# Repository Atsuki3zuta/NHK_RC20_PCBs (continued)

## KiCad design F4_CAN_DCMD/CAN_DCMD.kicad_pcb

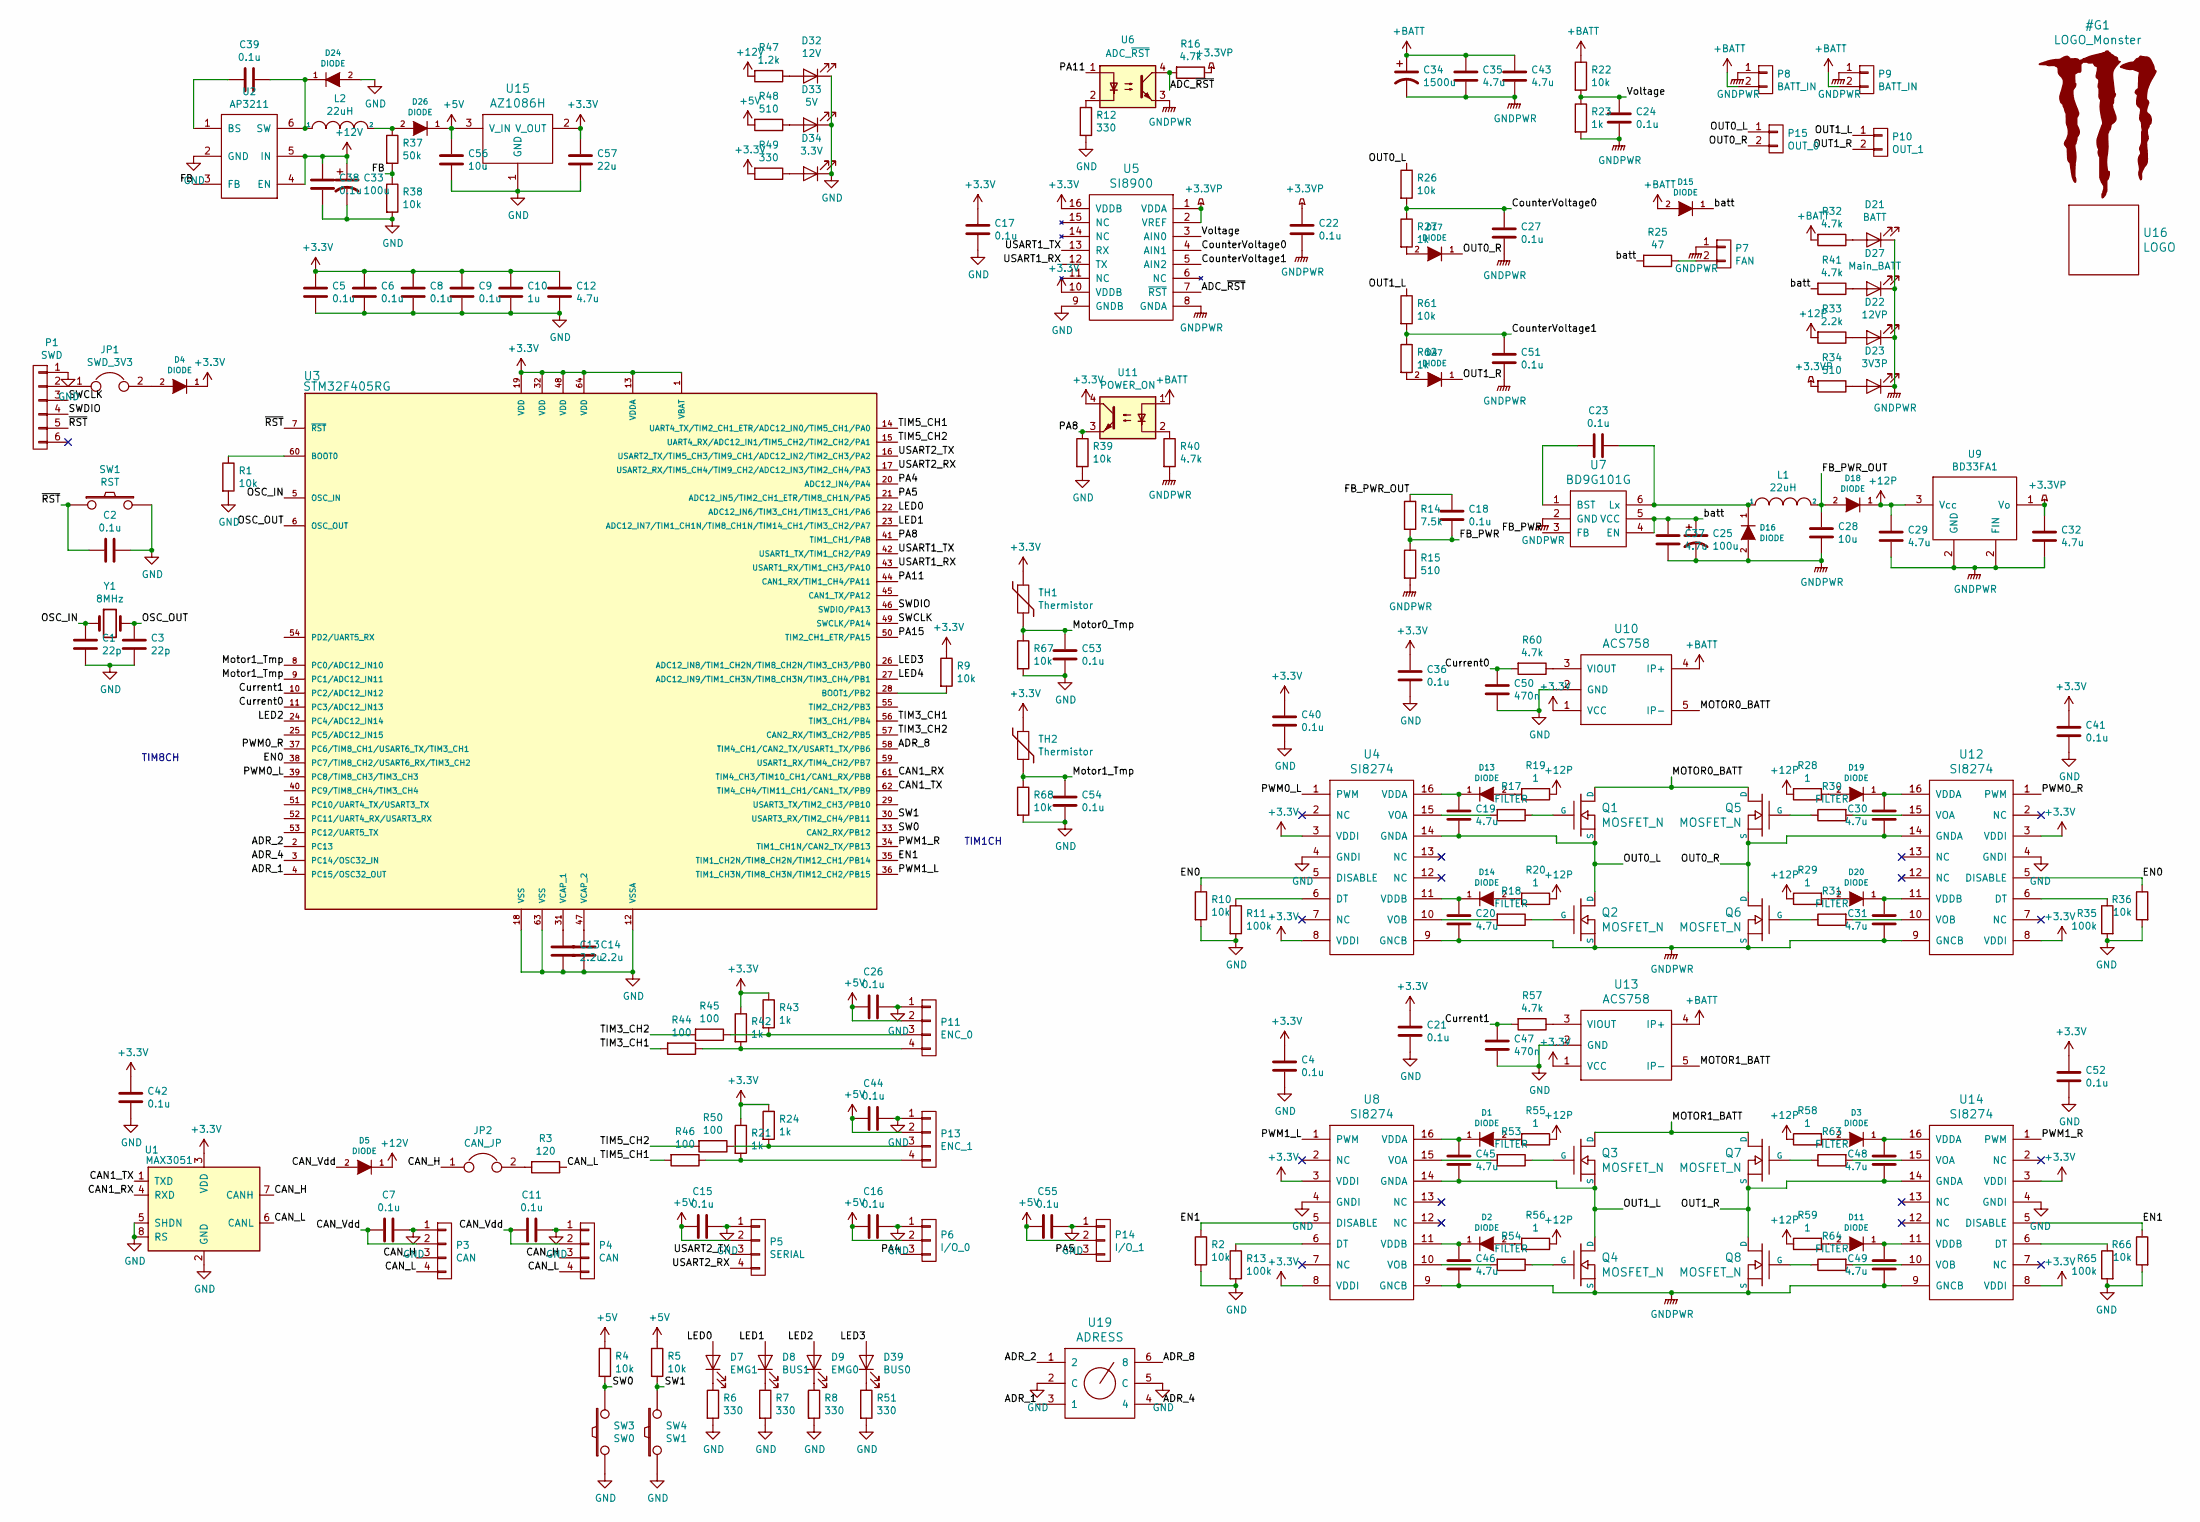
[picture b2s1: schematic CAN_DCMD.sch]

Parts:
C1, C3: 22p; C_0603_1608Metric
C2, C4, C5, C6, C7, C8, C9, C11, C15, C16, C17, C18, C21, C22, C23, C24, C26, C27, C36, C38, C39, C40, C41, C42, C44, C51, C52, C53, C54, C55: 0.1u; C_0603_1608Metric
C10: 1u; C_0603_1608Metric
C12: 4.7u; C_0603_1608Metric
C13, C14: 2.2u; C_0603_1608Metric
C19, C20, C30, C31, C45, C46, C48, C49: 4.7u; C_1210_3225Metric
C25, C33: 100u; CP_Radial_D5.0mm_P2.50mm
C28: 10u; C_0805_2012Metric
C29, C32, C35, C37, C43: 4.7u; C_0805_2012Metric
C34: 1500u; CP_Radial_D10.0mm_P5.00mm
C47, C50: 470n; C_0603_1608Metric
C56: 10u; C_0603_1608Metric
C57: 22u; C_0603_1608Metric
D1, D2, D3, D11, D13, D14, D19, D20: DIODE; D_0603_1608Metric
D4, D5, D16, D17, D18, D24, D26, D47: DIODE; D_SOD-123
D7: EMG1; LED_0603_1608Metric
D8: BUS1; LED_0603_1608Metric
D9: EMG0; LED_0603_1608Metric
D15: DIODE; D_SMA
D21: BATT; LED_0603_1608Metric
D22: 12VP; LED_0603_1608Metric
D23: 3V3P; LED_0603_1608Metric
D27: Main_BATT; LED_0603_1608Metric
D32: 12V; LED_0603_1608Metric
D33: 5V; LED_0603_1608Metric
D34: 3.3V; LED_0603_1608Metric
D39: BUS0; LED_0603_1608Metric
JP1: SWD_3V3; SolderJumper-2_P1.3mm_Open_TrianglePad1.0x1.5mm
JP2: CAN_JP; PinHeader_1x02_P2.54mm_Vertical
L1, L2: 22uH; Inductor_Taiyo-Yuden_NR-60xx_HandSoldering
P1: SWD; ZH_6P
P3, P4: CAN; XA_4LC
P5: SERIAL; XA_4LC
P6: I/O_0; XA_3LC
P7: FAN; XA_2P
P8: BATT_IN; XT60_M
P9: BATT_IN; XT60_F
P10: OUT_1; XT60_F
P11: ENC_0; XA_4LC
P13: ENC_1; XA_4LC
P14: I/O_1; XA_3LC
P15: OUT_0; XT60_F
Q1, Q2, Q3, Q4, Q5, Q6, Q7, Q8: MOSFET_N; D2-PAK_compact
R1, R2, R4, R5, R9, R10, R22, R26, R36, R38, R39, R61, R66, R67, R68: 10k; R_0603_1608Metric
R3: 120; R_0603_1608Metric
R6, R7, R8, R12, R49, R51: 330; R_0603_1608Metric
R11, R13, R35, R65: 100k; R_0603_1608Metric
R14: 7.5k; R_0603_1608Metric
R15, R34, R48: 510; R_0603_1608Metric
R16, R32, R40, R41, R57, R60: 4.7k; R_0603_1608Metric
R17, R18, R30, R31, R53, R54, R63, R64: FILTER; R_0603_1608Metric
R19, R20, R28, R29, R55, R56, R58, R59: 1; R_0603_1608Metric
R21, R23, R24, R27, R42, R43, R62: 1k; R_0603_1608Metric
R25: 47; R_2812
R33: 2.2k; R_0603_1608Metric
R37: 50k; R_0603_1608Metric
R44, R45, R46, R50: 100; R_0603_1608Metric
R47: 1.2k; R_0603_1608Metric
SW1: RST; SW_SPST_CK_RS282G05A3
SW3: SW0; SW_SPST_CK_RS282G05A3
SW4: SW1; SW_SPST_CK_RS282G05A3
TH1, TH2: Thermistor; C_0603_1608Metric
U1: MAX3051; SOIC-8_3.9x4.9mm_P1.27mm
U2: AP3211; TSOP-6_1.65x3.05mm_P0.95mm
U3: STM32F405RG; LQFP-64_10x10mm_P0.5mm
U4, U8, U12, U14: SI8274; SOIC-16W_5.3x10.2mm_P1.27mm
U5: SI8900; SOIC-16W_7.5x10.3mm_P1.27mm
U6: ADC_~RST; SO-4_4.4x2.3mm_P1.27mm
U7: BD9G101G; TSOP-6_1.65x3.05mm_P0.95mm
U9: BD33FA1; SOT-89-3
U10, U13: ACS758; ACS785xCB
U11: POWER_ON; SO-4_4.4x2.3mm_P1.27mm
U15: AZ1086H; SOT-223-3_TabPin2
U16: LOGO; Mini_Monster
U19: ADRESS; rotary_0F
Y1: 8MHz; Crystal_SMD_5032_2Pads

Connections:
+3.3VP: C22.1, C32.1, R16.1, R34.2, U5.1 (VDDA), U5.2 (VREF), U9.1 (Vo)
+3V3: C4.1, C5.1, C6.1, C8.1, C9.1, C10.1, C12.1, C17.1, C21.1, C36.1, C40.1, C41.1, C42.1, C52.1, C57.1, D4.1 (K), R9.1, R21.1, R24.1, R42.1, R43.1, R49.2, TH1.1, TH2.1, U1.3 (VDD), U3.1 (VBAT), U3.13 (VDDA), U3.19 (VDD), U3.32 (VDD), U3.48 (VDD), U3.64 (VDD), U4.3 (VDDI), U4.8 (VDDI), U5.10 (VDDB), U5.16 (VDDB), U8.3 (VDDI), U8.8 (VDDI), U10.1 (VCC), U11.4, U12.3 (VDDI), U12.8 (VDDI), U13.1 (VCC), U14.3 (VDDI), U14.8 (VDDI), U15.2 (V_OUT)
+5V: C15.2, C16.2, C26.2, C44.2, C55.2, C56.1, D26.1 (K), P5.2, P6.2, P11.2, P13.2, P14.2, R4.1, R5.1, R48.2, U15.3 (V_IN)
+12P: C29.1, D18.1 (K), R19.1, R20.1, R28.1, R29.1, R33.2, R55.1, R56.1, R58.1, R59.1, U9.3 (Vcc)
+12V: C33.1, C38.1, D5.1 (K), R47.2, U2.4 (EN), U2.5 (IN)
+BATT: C34.1, C35.1, C43.1, D15.2 (A), P8.2, P9.2, R22.1, R32.2, U10.4 (IP+), U11.1, U13.4 (IP+)
/ADC_~RST: R16.2, U5.7 (~RST~), U6.4
/ADR_1: U3.4 (PC15/OSC32_OUT), U19.3 (1)
/ADR_2: U3.2 (PC13), U19.1 (2)
/ADR_4: U3.3 (PC14/OSC32_IN), U19.4
/ADR_8: U3.58 (TIM4_CH1/CAN2_TX/USART1_TX/PB6), U19.6 (8)
/CAN1_RX: U1.4 (RXD), U3.61 (TIM4_CH3/TIM10_CH1/CAN1_RX/PB8)
/CAN1_TX: U1.1 (TXD), U3.62 (TIM4_CH4/TIM11_CH1/CAN1_TX/PB9)
/CAN_H: JP2.1, P3.3, P4.3, U1.7 (CANH)
/CAN_L: P3.4, P4.4, R3.1, U1.6 (CANL)
/CAN_Vdd: C7.2, C11.2, D5.2 (A), P3.2, P4.2
/CounterVoltage0: C27.1, R26.2, R27.1, U5.4 (AIN1)
/CounterVoltage1: C51.1, R61.2, R62.1, U5.5 (AIN2)
/Current0: C50.1, R60.2, U3.11 (PC3/ADC12_IN13)
/Current1: C47.1, R57.2, U3.10 (PC2/ADC12_IN12)
/EN0: R10.1, R36.1, U3.38 (PC7/TIM8_CH2/USART6_RX/TIM3_CH2), U4.5 (DISABLE), U12.5 (DISABLE)
/EN1: R2.1, R66.1, U3.35 (TIM1_CH2N/TIM8_CH2N/TIM12_CH1/PB14), U8.5 (DISABLE), U14.5 (DISABLE)
/FB: R37.2, R38.1, U2.3 (FB)
/FB_PWR: C18.2, R14.2, R15.1, U7.3 (FB)
/FB_PWR_OUT: C18.1, C28.1, D18.2 (A), L1.2, R14.1
/LED0: D7.2 (A), U3.22 (ADC12_IN6/TIM3_CH1/TIM13_CH1/PA6)
/LED1: D8.2 (A), U3.23 (ADC12_IN7/TIM1_CH1N/TIM8_CH1N/TIM14_CH1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)
/LED2: D9.2 (A), U3.24 (PC4/ADC12_IN14)
/LED3: D39.2 (A), U3.26 (ADC12_IN8/TIM1_CH2N/TIM8_CH2N/TIM3_CH3/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)
/LED4: U3.27 (ADC12_IN9/TIM1_CH3N/TIM8_CH3N/TIM3_CH4/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)
/MOTOR0_BATT: Q1.D, Q5.D, U10.5 (IP-)
/MOTOR1_BATT: Q3.D, Q7.D, U13.5 (IP-)
/Motor0_Tmp: C53.1, R67.1, TH1.2
/Motor1_Tmp: C54.1, R68.1, TH2.2, U3.8 (PC0/ADC12_IN10), U3.9 (PC1/ADC12_IN11)
/OSC_IN: C1.2, U3.5 (OSC_IN), Y1.1
/OSC_OUT: C3.2, U3.6 (OSC_OUT), Y1.2
/OUT0_L: C19.2, P15.1, Q1.S, Q2.D, R26.1, U4.14 (GNDA)
/OUT0_R: C30.2, D17.1 (K), P15.2, Q5.S, Q6.D, U12.14 (GNDA)
/OUT1_L: C45.2, P10.1, Q3.S, Q4.D, R61.1, U8.14 (GNDA)
/OUT1_R: C48.2, D47.1 (K), P10.2, Q7.S, Q8.D, U14.14 (GNDA)
/PA4: P6.3, U3.20 (ADC12_IN4/PA4)
/PA5: P14.3, U3.21 (ADC12_IN5/TIM2_CH1_ETR/TIM8_CH1N/PA5)
/PA8: R39.1, U3.41 (TIM1_CH1/PA8), U11.3
/PA11: U3.44 (CAN1_RX/TIM1_CH4/PA11), U6.1
/PA15: U3.50 (TIM2_CH1_ETR/PA15)
/PWM0_L: U3.39 (PC8/TIM8_CH3/TIM3_CH3), U4.1 (PWM)
/PWM0_R: U3.37 (PC6/TIM8_CH1/USART6_TX/TIM3_CH1), U12.1 (PWM)
/PWM1_L: U3.36 (TIM1_CH3N/TIM8_CH3N/TIM12_CH2/PB15), U8.1 (PWM)
/PWM1_R: U3.34 (TIM1_CH1N/CAN2_TX/PB13), U14.1 (PWM)
/SW0: R4.2, SW3.2, U3.33 (CAN2_RX/PB12)
/SW1: R5.2, SW4.2, U3.30 (USART3_RX/TIM2_CH4/PB11)
/SWCLK: P1.3, U3.49 (SWCLK/PA14)
/SWDIO: P1.4, U3.46 (SWDIO/PA13)
/TIM3_CH1: R44.2, U3.56 (TIM3_CH1/PB4)
/TIM3_CH2: R45.2, U3.57 (CAN2_RX/TIM3_CH2/PB5)
/TIM5_CH1: R46.2, U3.14 (UART4_TX/TIM2_CH1_ETR/ADC12_IN0/TIM5_CH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)
/TIM5_CH2: R50.2, U3.15 (UART4_RX/ADC12_IN1/TIM5_CH2/TIM2_CH2/PA1)
/USART1_RX: U3.43 (USART1_RX/TIM1_CH3/PA10), U5.12 (TX)
/USART1_TX: U3.42 (USART1_TX/TIM1_CH2/PA9), U5.13 (RX)
/USART2_RX: P5.4, U3.17 (USART2_RX/TIM5_CH4/TIM9_CH2/ADC12_IN3/T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)
/USART2_TX: P5.3, U3.16 (USART2_TX/TIM5_CH3/TIM9_CH1/ADC12_IN2/T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)
/Voltage: C24.1, R22.2, R23.1, U5.3 (AIN0)
/batt: C25.1, C37.1, D15.1 (K), R25.2, R41.2, U7.4 (EN), U7.5 (VCC)
/~RST: C2.2, P1.5, SW1.1, U3.7 (~RST)
GND: C1.1, C2.1, C3.1, C4.2, C5.2, C6.2, C7.1, C8.2, C9.2, C10.2, C11.1, C12.2, C13.2, C14.2, C15.1, C16.1, C17.2, C21.2, C26.1, C33.2, C36.2, C38.2, C40.2, C41.2, C42.2, C44.1, C47.2, C50.2, C52.2, C53.2, C54.2, C55.1, C56.2, C57.2, D24.2 (A), D32.1 (K), D33.1 (K), D34.1 (K), P1.1, P3.1, P4.1, P5.1, P6.1, P11.1, P13.1, P14.1, R1.2, R2.2, R6.2, R7.2, R8.2, R10.2, R11.2, R12.2, R13.2, R35.2, R36.2, R38.2, R39.2, R51.2, R65.2, R66.2, R67.2, R68.2, SW1.2, SW3.1, SW4.1, U1.2 (GND), U1.5 (SHDN), U1.8 (RS), U2.2 (GND), U3.12 (VSSA), U3.18 (VSS), U3.63 (VSS), U4.4 (GNDI), U5.9 (GNDB), U8.4 (GNDI), U10.2 (GND), U12.4 (GNDI), U13.2 (GND), U14.4 (GNDI), U15.1 (GND), U19.2 (C), U19.5 (C)
GNDPWR: C20.2, C22.2, C24.2, C25.2, C27.2, C28.2, C29.2, C31.2, C32.2, C34.2, C35.2, C37.2, C43.2, C46.2, C49.2, C51.2, D16.2 (A), D21.1 (K), D22.1 (K), D23.1 (K), D27.1 (K), P7.1, P8.1, P9.1, Q2.S, Q4.S, Q6.S, Q8.S, R15.2, R23.2, R40.2, U4.9 (GNCB), U5.8 (GNDA), U6.3, U7.2 (GND), U8.9 (GNCB), U9.2 (FIN), U12.9 (GNCB), U14.9 (GNCB)
unnamed: C13.1, U3.31 (VCAP_1)
unnamed: C14.1, U3.47 (VCAP_2)
unnamed: C19.1, D13.1 (K), U4.16 (VDDA)
unnamed: C20.1, D14.1 (K), U4.11 (VDDB)
unnamed: C23.1, D16.1 (K), L1.1, U7.6 (Lx)
unnamed: C23.2, U7.1 (BST)
unnamed: C30.1, D19.1 (K), U12.16 (VDDA)
unnamed: C31.1, D20.1 (K), U12.11 (VDDB)
unnamed: C39.1, D24.1 (K), L2.1, U2.6 (SW)
unnamed: C39.2, U2.1 (BS)
unnamed: C45.1, D1.1 (K), U8.16 (VDDA)
unnamed: C46.1, D2.1 (K), U8.11 (VDDB)
unnamed: C48.1, D3.1 (K), U14.16 (VDDA)
unnamed: C49.1, D11.1 (K), U14.11 (VDDB)
unnamed: D1.2 (A), R55.2
unnamed: D2.2 (A), R56.2
unnamed: D3.2 (A), R58.2
unnamed: D4.2 (A), JP1.2
unnamed: D7.1 (K), R6.1
unnamed: D8.1 (K), R7.1
unnamed: D9.1 (K), R8.1
unnamed: D11.2 (A), R59.2
unnamed: D13.2 (A), R19.2
unnamed: D14.2 (A), R20.2
unnamed: D17.2 (A), R27.2
unnamed: D19.2 (A), R28.2
unnamed: D20.2 (A), R29.2
unnamed: D21.2 (A), R32.1
unnamed: D22.2 (A), R33.1
unnamed: D23.2 (A), R34.1
unnamed: D26.2 (A), L2.2, R37.1
unnamed: D27.2 (A), R41.1
unnamed: D32.2 (A), R47.1
unnamed: D33.2 (A), R48.1
unnamed: D34.2 (A), R49.1
unnamed: D39.1 (K), R51.1
unnamed: D47.2 (A), R62.2
unnamed: JP1.1, P1.2
unnamed: JP2.2, R3.2
unnamed: P7.2, R25.1
unnamed: P11.3, R43.2, R45.1
unnamed: P11.4, R42.2, R44.1
unnamed: P13.3, R24.2, R50.1
unnamed: P13.4, R21.2, R46.1
unnamed: Q1.G, R17.1
unnamed: Q2.G, R18.1
unnamed: Q3.G, R53.1
unnamed: Q4.G, R54.1
unnamed: Q5.G, R30.1
unnamed: Q6.G, R31.1
unnamed: Q7.G, R63.1
unnamed: Q8.G, R64.1
unnamed: R1.1, U3.60 (BOOT0)
unnamed: R9.2, U3.28 (BOOT1/PB2)
unnamed: R11.1, U4.6 (DT)
unnamed: R12.1, U6.2
unnamed: R13.1, U8.6 (DT)
unnamed: R17.2, U4.15 (VOA)
unnamed: R18.2, U4.10 (VOB)
unnamed: R30.2, U12.15 (VOA)
unnamed: R31.2, U12.10 (VOB)
unnamed: R35.1, U12.6 (DT)
unnamed: R40.1, U11.2
unnamed: R53.2, U8.15 (VOA)
unnamed: R54.2, U8.10 (VOB)
unnamed: R57.1, U13.3 (VIOUT)
unnamed: R60.1, U10.3 (VIOUT)
unnamed: R63.2, U14.15 (VOA)
unnamed: R64.2, U14.10 (VOB)
unnamed: R65.1, U14.6 (DT)

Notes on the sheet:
TIM1CH
TIM8CH

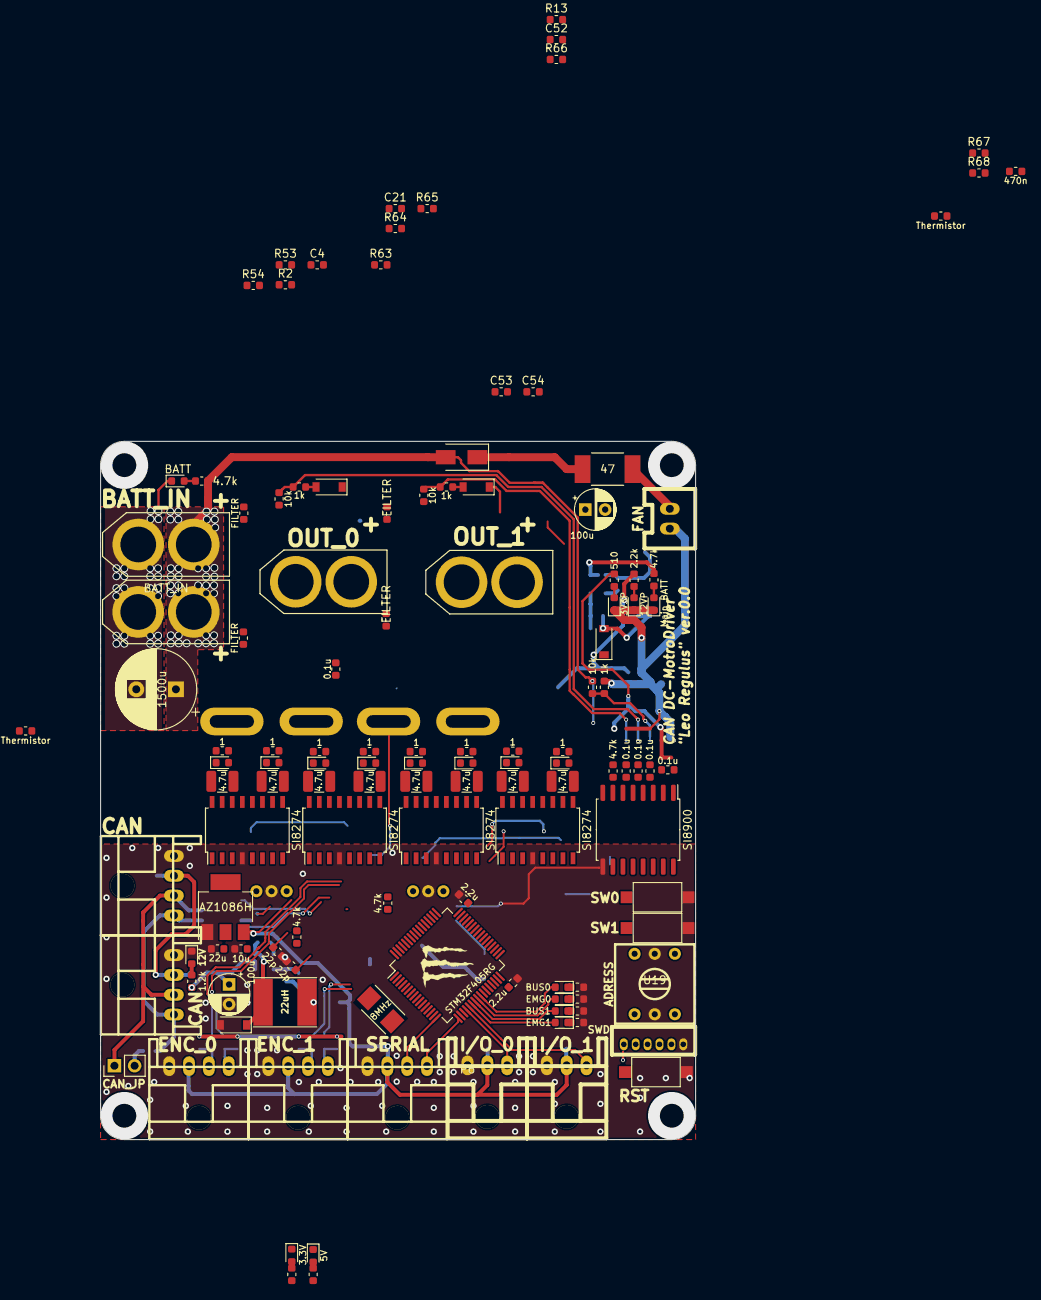
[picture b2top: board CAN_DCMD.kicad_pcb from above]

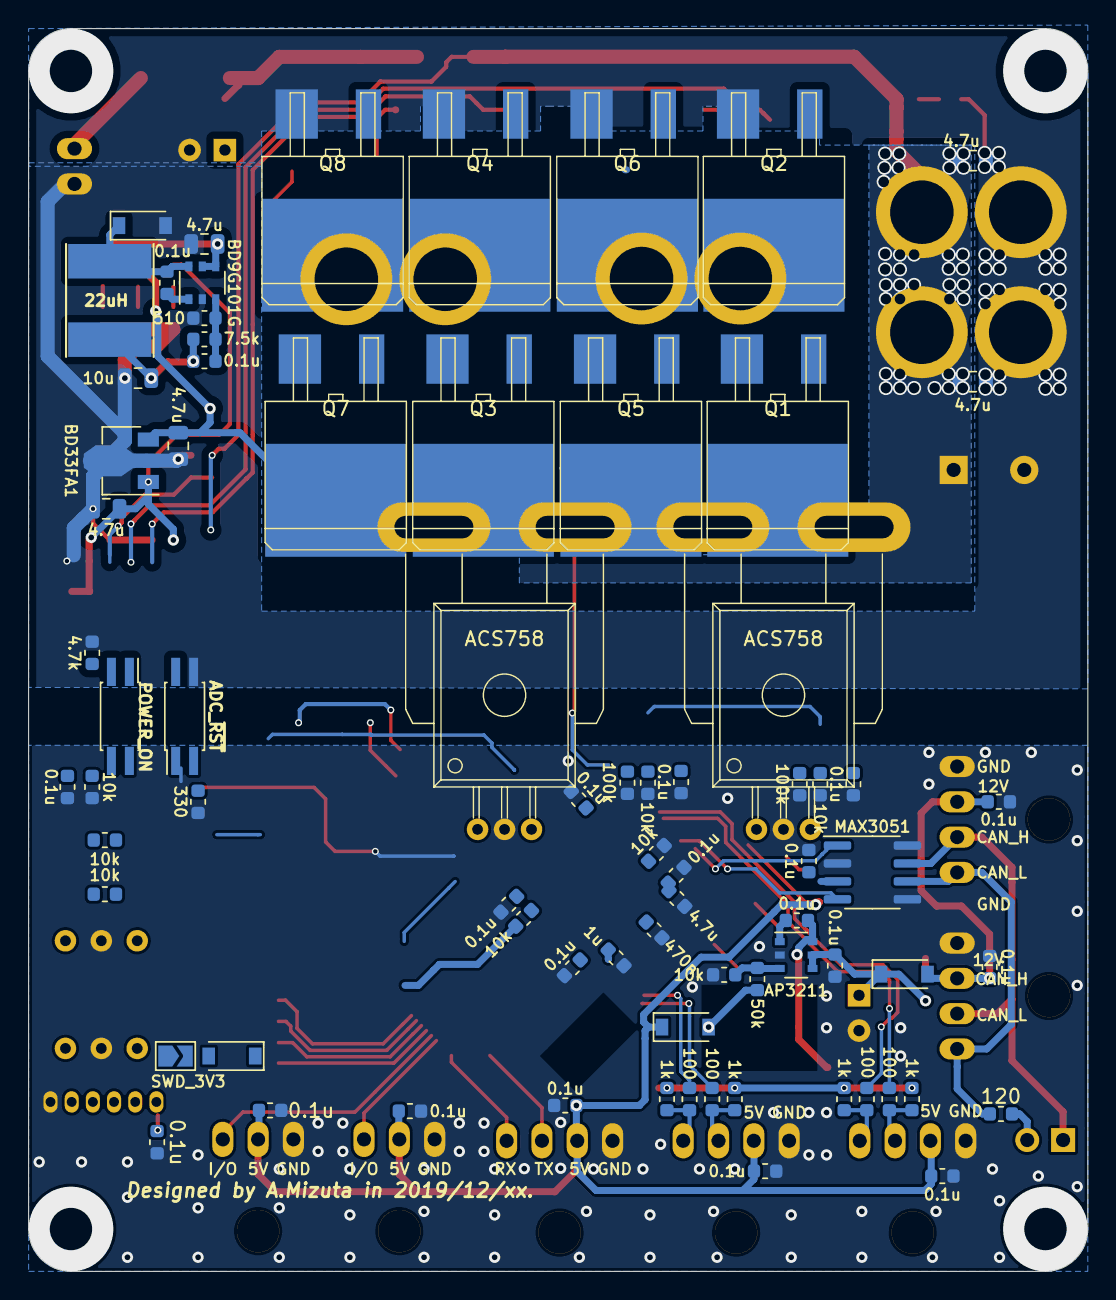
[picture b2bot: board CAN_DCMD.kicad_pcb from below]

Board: 2 copper layers, 75.0 x 88.0 mm, 200 parts (75 on the bottom side), 134 nets.

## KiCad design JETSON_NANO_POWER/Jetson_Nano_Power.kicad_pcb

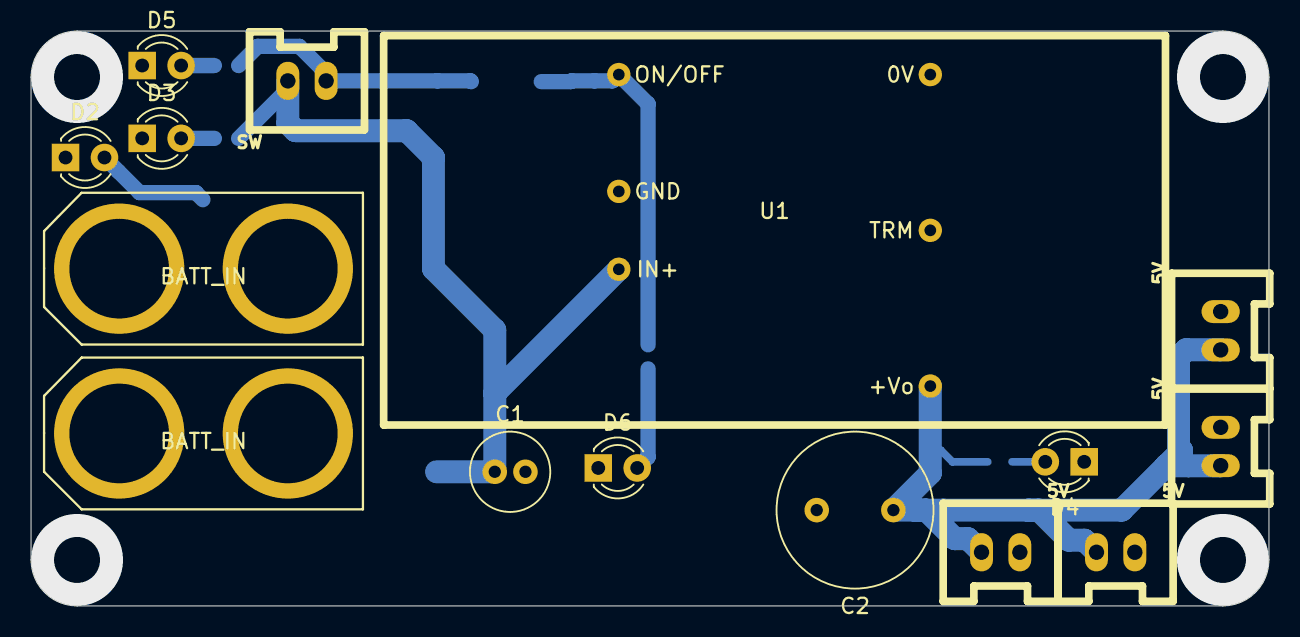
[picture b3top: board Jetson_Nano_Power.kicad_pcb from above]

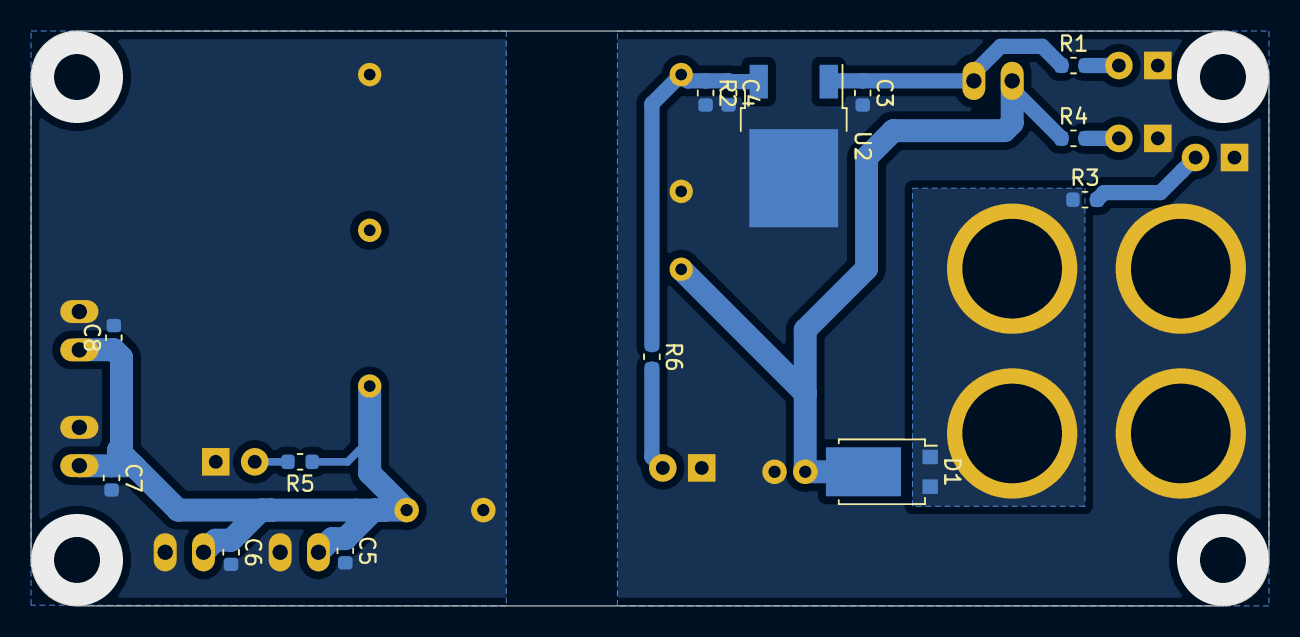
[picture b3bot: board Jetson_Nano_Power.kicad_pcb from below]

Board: 2 copper layers, 80.8 x 37.5 mm, 29 parts (14 on the bottom side), 12 nets.

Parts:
C1: 100u; C_Radial_D5.0mm_H11.0mm_P2.00mm
C2: 470u; C_Radial_D10.0mm_H16.0mm_P5.00mm
C3, C4: 0.1u; C_0603_1608Metric
C5, C6, C7, C8: C; C_0603_1608Metric
D1: SBRDIODE; TO-277B
D2, D3, D4, D5, D6: LED; LED_D3.0mm
P1, P5, P6, P7: 5V; XA_2P
P2: SW; XA_2P
P3, P4: BATT_IN; XT90PB
R1, R3, R4: 4.7k; R_0603_1608Metric
R2: 10k; R_0603_1608Metric
R5, R6: 510; R_0603_1608Metric
U1: VYB20W-Q24-S5
U2: BA17805FP; TO-252-2

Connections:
+5V: C2.1, C5.1, C6.1, C7.1, C8.1, P1.2, P5.2, P6.2, P7.2, R5.1, U1.3
+5VP: C4.1, R2.1, R6.1, U1.6, U2.3
+BATT: D1.1, D1.2, P3.2, P4.2, R3.1
GND: C2.2, C5.2, C6.2, C7.2, C8.2, D4.1, P1.1, P5.1, P6.1, P7.1, U1.5
GNDPWR: C1.2, C3.2, C4.2, D2.1, D3.1, D5.1, D6.1, P3.1, P4.1, R2.2, U1.1, U2.2
MAIN_OUT: C1.1, D1.3, P2.1, R4.1, U1.2
unnamed: D2.2, R3.2
unnamed: D3.2, R4.2
unnamed: D4.2, R5.2
unnamed: D5.2, R1.2
unnamed: D6.2, R6.2
batt+: C3.1, P2.2, R1.1, U2.1
